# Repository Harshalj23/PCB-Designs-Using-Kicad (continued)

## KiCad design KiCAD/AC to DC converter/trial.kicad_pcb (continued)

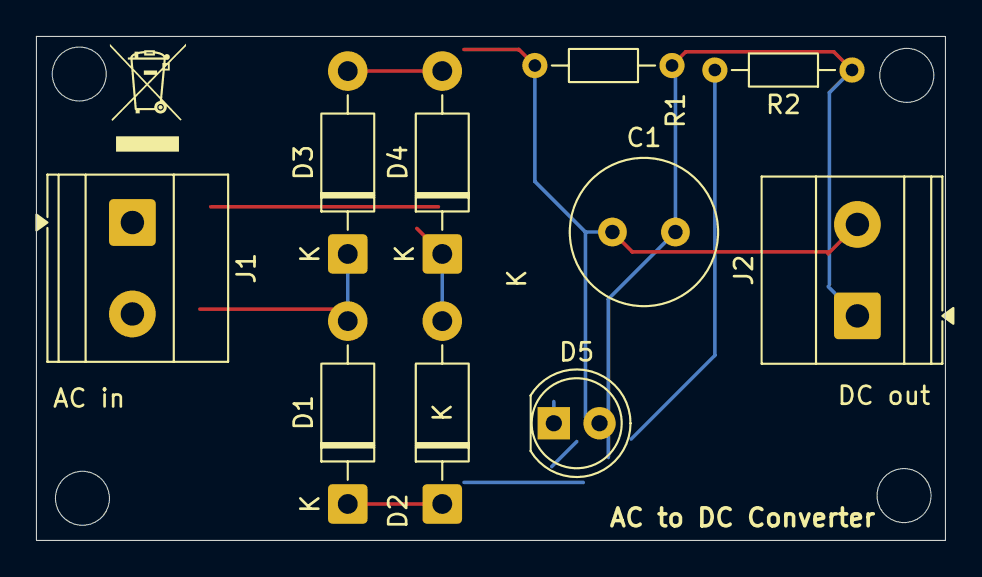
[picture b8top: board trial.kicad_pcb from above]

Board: 2 copper layers, 50.5 x 28.0 mm, 10 parts (0 on the bottom side), 5 nets.

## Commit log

2026-01-02 Initial upload of KiCad projects
2026-01-02 Add KiCad gitignore
2026-01-02 Readme Added
